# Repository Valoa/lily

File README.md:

# lily

Lily, will be the water version of the pixi. old pixi files found on https://github.com/HermanKopinga/Buren/

- new hardware is added, to allow the pixi to readout 2 lipo voltage protectors, and controll an 40v powerled
- hardware is made so that it fits under the original pixi using A3 and pin 5 on the pixi pcb
- also the powerled will have small pcb cast in epoxy that wil be partly "water cooled"

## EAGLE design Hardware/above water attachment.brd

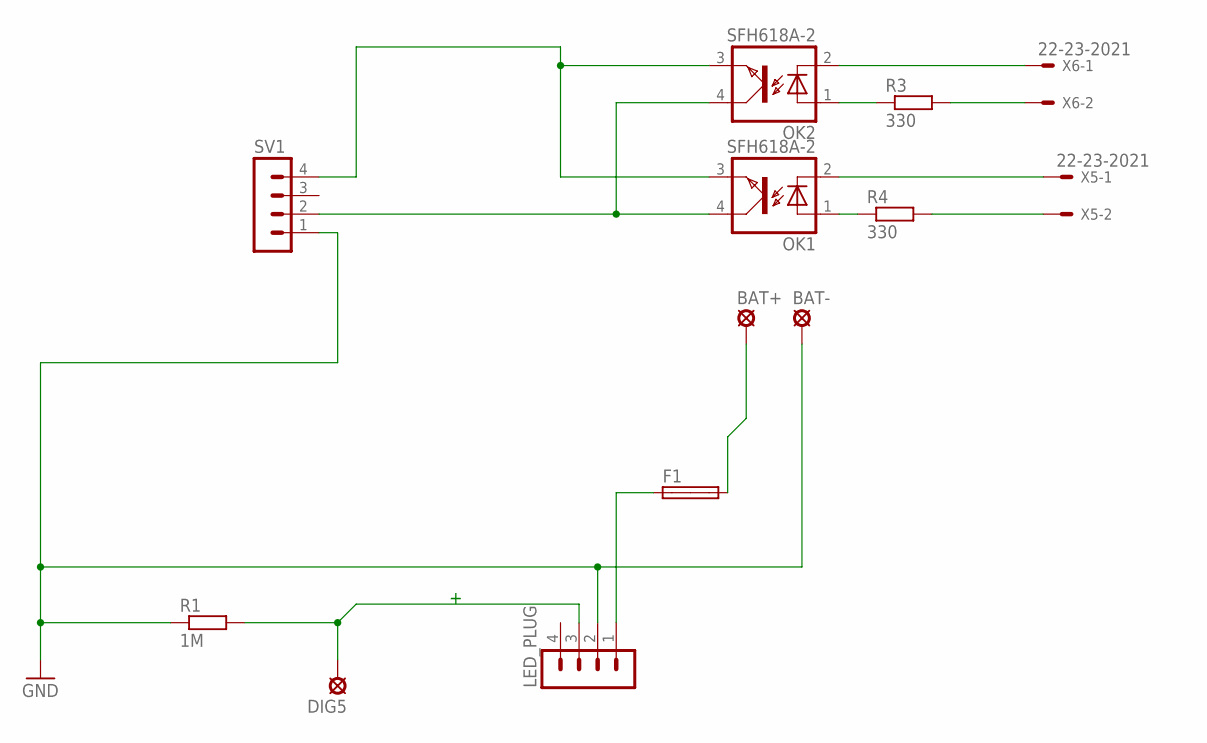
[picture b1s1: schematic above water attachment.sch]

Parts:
BAT+: bat+; SE14
BAT-: Bat-; SE14
DIG5: Led-; SE14
F1: SHK20Q
LED_PLUG: MA04-1
OK1, OK2: SFH618A-2; DIP4
R1: 1M; R2512
R3, R4: 330; R1206
SV1: MA04-1
X5, X6: 22-23-2021

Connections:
GND: BAT-.MP, LED_PLUG.2, R1.1, SV1.1
unnamed: OK1.4 (COL), OK2.4 (COL), SV1.2
unnamed: BAT+.MP, F1.2A
unnamed: DIG5.MP, LED_PLUG.3, R1.2
unnamed: OK1.3 (EMIT), OK2.3 (EMIT), SV1.4
unnamed: R4.2, X5.2
unnamed: R3.2, X6.2
unnamed: OK2.2 (C), X6.1
unnamed: OK1.2 (C), X5.1
unnamed: OK1.1 (A), R4.1
unnamed: OK2.1 (A), R3.1
unnamed: F1.1A, LED_PLUG.1

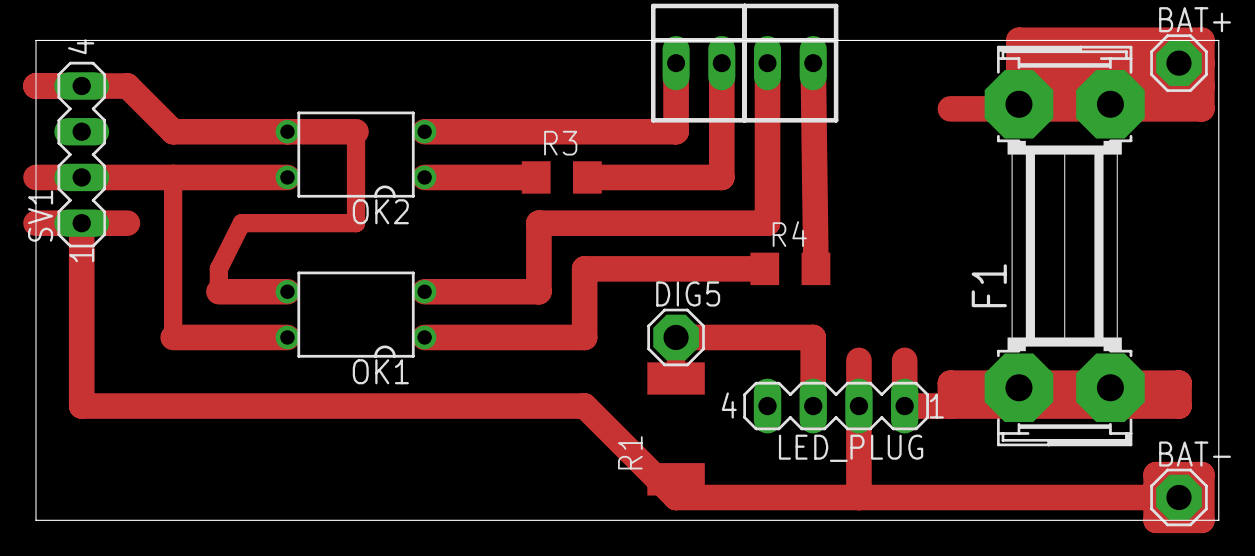
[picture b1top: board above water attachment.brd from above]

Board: 2 copper layers, 65.7 x 26.7 mm, 13 parts (0 on the bottom side), 12 nets.

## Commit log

2016-06-17 Lily setup
    the to be updated “buren” code
2016-06-17 added hardware files
    the pcb fits on the bottom of the original pixie, it allows for lipo
    alarm reading thru optocouplers, and control of the 40v powerled
2016-06-30 new lib for rf
    this is just a backup for the work stat starts now
2016-06-30 minor changes
2016-06-30 new lib for rf
2016-06-30 powerled fade+ alarm
    small powerled fade tester for, the lipo+powerled, also a lipo battery
    alarm reader.
2016-07-04 New Flock update.
    Full flocking behaviour based on dropped packets, master and slave are
    changeable by just one bit on the bottom of the lilly.cpp.
    also senders are updateble from the shore.
    Big thanx to David Koster for making it happen
2016-07-04 change title
2016-07-05 updated the pcb_epoxi and master controller
    master controller is used to control the powerled and control the lily’s
2016-07-05 bool for powerled show alarm
    else lily’s without powerled will show color
2016-07-05 whoops, declared iHavePowerled()
2016-07-07 added an masterController
    masterController sets chances in the sender
